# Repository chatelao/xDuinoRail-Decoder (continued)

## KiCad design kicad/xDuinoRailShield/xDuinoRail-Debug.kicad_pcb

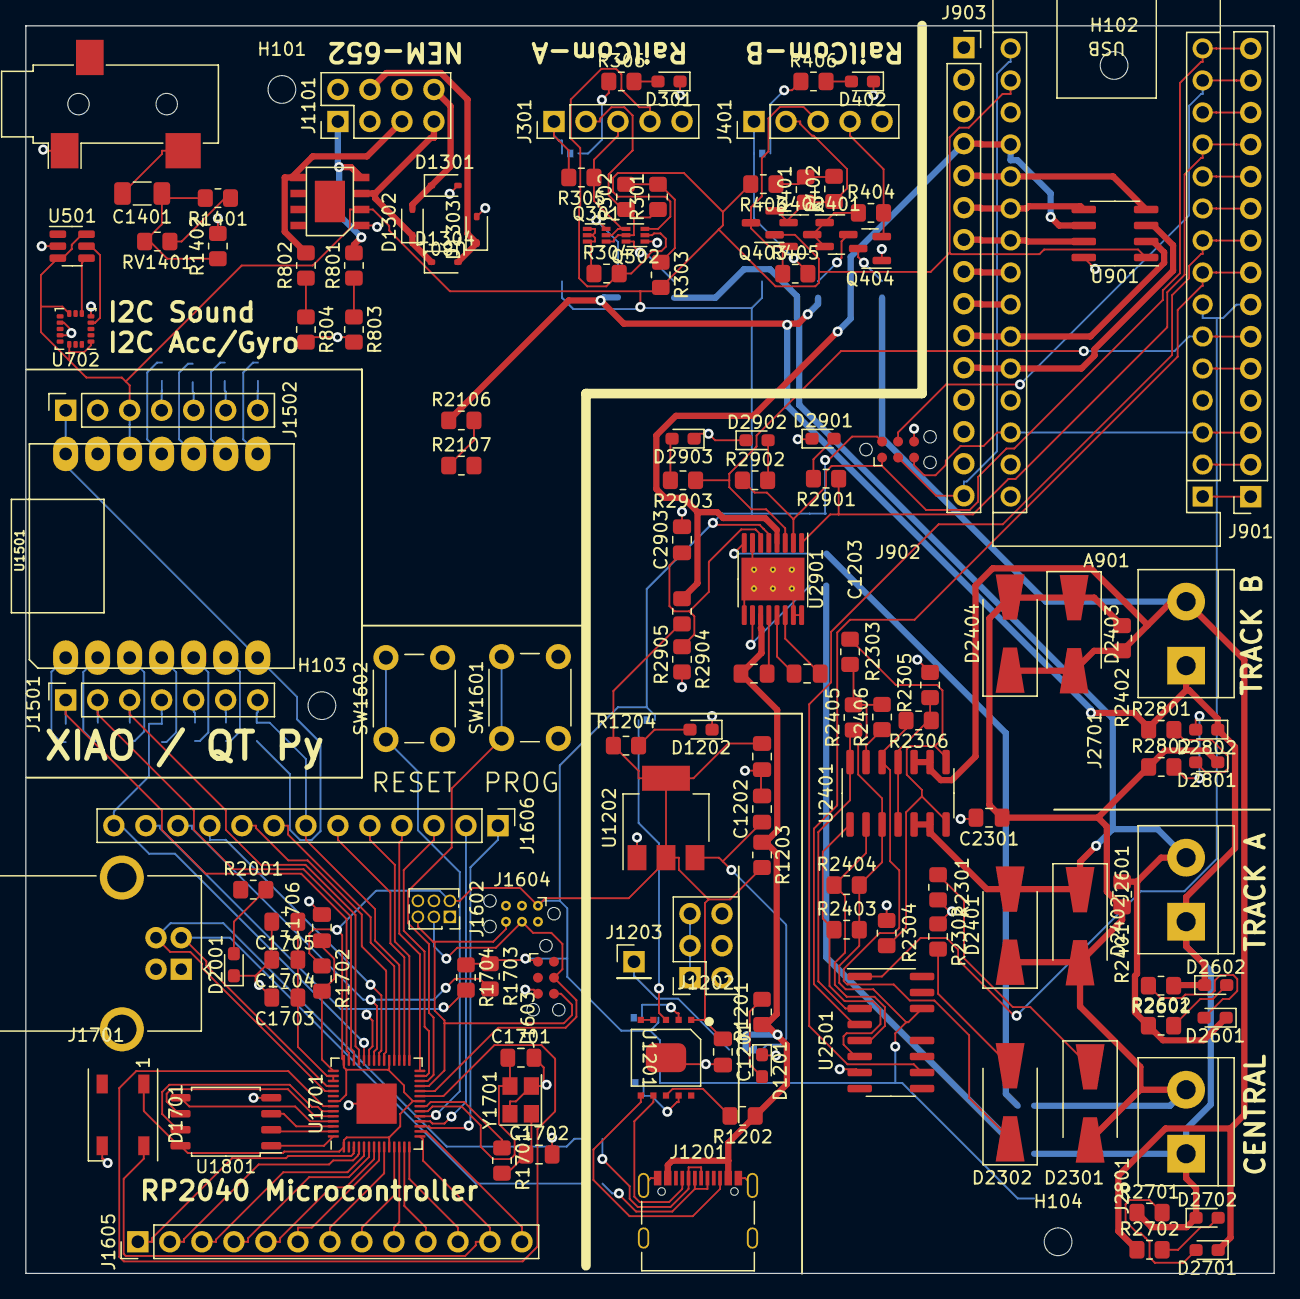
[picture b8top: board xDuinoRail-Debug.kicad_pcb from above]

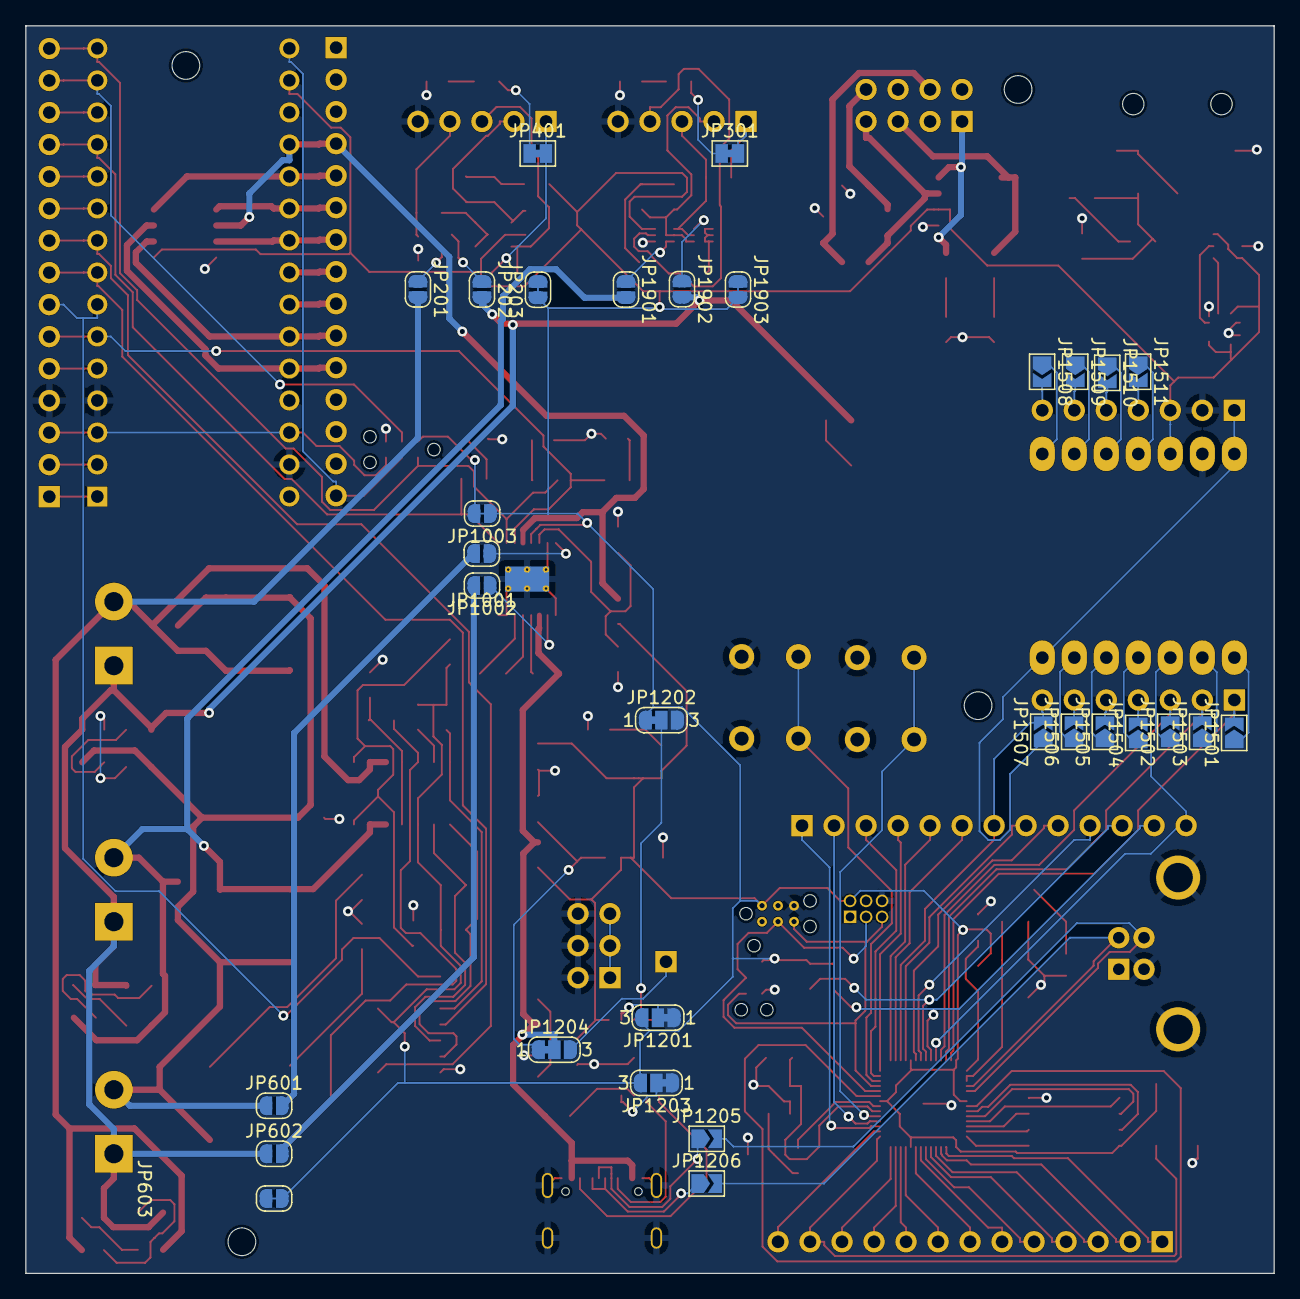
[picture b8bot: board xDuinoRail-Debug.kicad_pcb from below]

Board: 2 copper layers, 99.1 x 99.0 mm, 170 parts (31 on the bottom side), 168 nets.

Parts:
A901: Arduino_Nano_Every; Arduino_Nano
C1201, C1202: 1uF; C_0805_2012Metric_Pad1.18x1.45mm_HandSolder
C1203, C2301: 47uF; C_0805_2012Metric_Pad1.18x1.45mm_HandSolder
C1401: 100uF; C_1206_3216Metric_Pad1.33x1.80mm_HandSolder
C1701, C1702: 33p; C_0805_2012Metric_Pad1.18x1.45mm_HandSolder
C1703, C1704: 100n; C_0805_2012Metric_Pad1.18x1.45mm_HandSolder
C1705, C1706: 10u; C_0805_2012Metric_Pad1.18x1.45mm_HandSolder
C2901: 100nF; C_0805_2012Metric_Pad1.18x1.45mm_HandSolder
C2902, C2903: 22nF; C_0805_2012Metric_Pad1.18x1.45mm_HandSolder
D301, D402, D1201, D1202, D2001, D2601, D2602, D2701, D2702, D2801, D2802: LED; LED_0603_1608Metric_Pad1.05x0.95mm_HandSolder
D1301, D1302, D1303, D1304: 1N5819WS; D_SOD-323
D1701: WS2812B; LED_WS2812B_PLCC4_5.0x5.0mm_P3.2mm
D2301, D2302: SM4007; D_SMA-SMB_Universal_Handsoldering
D2401, D2402, D2403, D2404: SS54; D_SMA-SMB_Universal_Handsoldering
D2901: LED_RED; LED_0603_1608Metric_Pad1.05x0.95mm_HandSolder
D2902: LED_YELLOW; LED_0603_1608Metric_Pad1.05x0.95mm_HandSolder
D2903: LED_GREEN; LED_0603_1608Metric_Pad1.05x0.95mm_HandSolder
H101, H102, H103, H104: MountingHole; MountingHole_2.2mm_M2
J301, J401: Conn_01x05; PinHeader_1x05_P2.54mm_Vertical
J901, J903: Conn_01x15; PinSocket_1x15_P2.54mm_Vertical
J902, J1603: Conn_ARM_SWD_TagConnect_TC2030-NL; Tag-Connect_TC2030-IDC-NL_2x03_P1.27mm_Vertical
J1101: Conn_02x04_Counter_Clockwise; PinHeader_2x04_P2.54mm_Vertical
J1201: USB_C_Receptacle_USB2.0_14P; USB_C_Receptacle_Palconn_UTC16-G
J1202: Conn_02x03_Odd_Even; PinSocket_2x03_P2.54mm_Vertical
J1203: Conn_01x01; PinHeader_1x01_P2.54mm_Vertical
J1401: AudioJack2_Ground; Jack_3.5mm_CUI_SJ-3523-SMT_Horizontal
J1501, J1502: Conn_01x07; PinSocket_1x07_P2.54mm_Vertical
J1602: Conn_02x03_Odd_Even; PinSocket_2x03_P1.27mm_Vertical
J1604: Conn_ARM_SWD_TagConnect_TC2030-NL; Tag-Connect_TC2030-IDC-NL_2x03_P1.27mm_Vertical-WithHoles
J1605, J1606: Conn_01x13; PinHeader_1x13_P2.54mm_Vertical
J1701: USB_B; USB_B_OST_USB-B1HSxx_Horizontal
J2601, J2701, J2801: Screw_Terminal_01x02; TerminalBlock_bornier-2_P5.08mm
JP201, JP202, JP203, JP601, JP602, JP603, JP1001, JP1002, JP1003, JP1901, JP1902, JP1903: SolderJumper_2_Open; SolderJumper-2_P1.3mm_Open_RoundedPad1.0x1.5mm
JP301, JP401: SolderJumper_2_Bridged; SolderJumper-2_P1.3mm_Bridged_Pad1.0x1.5mm
JP1201: CFG2; SolderJumper-3_P1.3mm_Bridged12_RoundedPad1.0x1.5mm_NumberL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
JP1202: CFG3; SolderJumper-3_P1.3mm_Bridged12_RoundedPad1.0x1.5mm_NumberL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
JP1203, JP1204: CFG1; SolderJumper-3_P1.3mm_Bridged12_RoundedPad1.0x1.5mm_NumberL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
JP1205, JP1206, JP1501, JP1502, JP1503, JP1504, JP1505, JP1506, JP1507, JP1508, JP1509, JP1510, JP1511: SolderJumper_2_Open; SolderJumper-2_P1.3mm_Open_TrianglePad1.0x1.5mm
Q301, Q302: BC847BVN; SOT-563
Q401, Q404: S8050; SOT-23
Q402, Q403: S8550; SOT-23
R301, R302, R303, R401, R402, R403: 10R; R_0805_2012Metric_Pad1.20x1.40mm_HandSolder
R304, R305, R404, R405, R1202, R1401, R1402, R1703, R1704, R2106, R2107, R2403, R2404, R2405, R2406: 10k; R_0805_2012Metric_Pad1.20x1.40mm_HandSolder
R306, R406, R1204: 100R; R_0805_2012Metric_Pad1.20x1.40mm_HandSolder
R801, R802: 6k8; R_0805_2012Metric_Pad1.20x1.40mm_HandSolder
R803, R804, R1201, R1203, R1701, R2304: 1k; R_0805_2012Metric_Pad1.20x1.40mm_HandSolder
R1702, R2301, R2302: 220R; R_0805_2012Metric_Pad1.20x1.40mm_HandSolder
R2001, R2901, R2902, R2903: 470R; R_0805_2012Metric_Pad1.20x1.40mm_HandSolder
R2303: 180K; R_0805_2012Metric_Pad1.20x1.40mm_HandSolder
R2305: 820R; R_0805_2012Metric_Pad1.20x1.40mm_HandSolder
R2306: 33k; R_0805_2012Metric_Pad1.20x1.40mm_HandSolder
R2401, R2402: 1R8; R_0805_2012Metric_Pad1.20x1.40mm_HandSolder
R2601, R2602, R2701, R2702, R2801, R2802: 3k3; R_0805_2012Metric_Pad1.20x1.40mm_HandSolder
R2904: 1k5; R_0805_2012Metric_Pad1.20x1.40mm_HandSolder
R2905: 47k; R_0805_2012Metric_Pad1.20x1.40mm_HandSolder
RV1401: 10k; R_0805_2012Metric_Pad1.20x1.40mm_HandSolder
SW1601, SW1602: SW_Push; SW_PUSH_6mm
U501: MCP4725xxx-xCH; SOT-23-6
U702: LIS3DH; LGA-16_3x3mm_P0.5mm_LayoutBorder3x5y
U801: BDR6133
U901: ATtiny402-SS; SOIC-8_3.9x4.9mm_P1.27mm
U1201: CH224K
U1202: AMS1117-3.3; SOT-223-3_TabPin2
U1501: MOUDLE-SEEEDUINO-XIAO-ESP32C3; MOUDLE14P-SMD-2.54-21X17.8MM
U1701: RP2040; QFN-56-1EP_7x7mm_P0.4mm_EP3.2x3.2mm
U1801: W25Q128JVS; SOIC-8_5.23x5.23mm_P1.27mm
U2401: LM339; SOIC-14_3.9x8.7mm_P1.27mm
U2501: 74HC02; SOIC-14-16_3.9x9.9mm_P1.27mm
U2901: DRV8874PWPR; HTSSOP-16-1EP_4.4x5mm_P0.65mm_EP3.4x5mm_Mask2.46x2.31mm_The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
Y1701: X322512MSB4SI; Crystal_SMD_3225-4Pin_3.2x2.5mm

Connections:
18mV: R2303.1, R2304.2, U2401.7 (+), U2401.8 (-)
+1V1: C1703.1, C1704.1, C1705.1, U1701.44 (VREG_IN), U1701.45 (VREG_VOUT)
+3V3: A901.17 (3V3), C1201.1, C1203.1, D1701.1 (VDD), J902.2 (SWDIO), J1502.3, J1602.2, J1603.1 (VCC), J1604.1 (VCC), JP203.1 (A), JP203.2 (B), JP603.1 (A), JP603.2 (B), JP1003.1 (A), JP1003.2 (B), JP1201.3 (B), JP1202.1 (A), JP1203.3 (B), JP1903.1 (A), JP1903.2 (B), Q302.3 (C2), Q403.1 (E), R303.2, R403.2, R1203.2, R1204.1, R1702.1, R1703.1, R1704.1, R2303.2, R2403.2, R2404.2, R2405.2, R2406.2, R2905.1, U501.3 (VDD), U501.6 (A0), U702.1 (VDD_IO), U702.8 (CS), U702.14 (VDD), U801.2 (VCC), U901.1 (VCC), U1201.1 (VDD), U1202.2 (VO), U1501.12 (3V3), U1701.1 (IOVDD), U1701.10 (IOVDD), U1701.22 (IOVDD), U1701.33 (IOVDD), U1701.42 (IOVDD), U1701.49 (IOVDD), U1801.8 (VCC), U2401.3 (V+), U2501.14 (VCC), U2901.5 (VRef)
+5V: J1502.1, JP1507.1 (A), U1501.7 (A6_TX), U1501.14 (5V)
+U: D1302.1 (K), D1304.1 (K), J1101.7, U801.3 (VM)
+VBUS_H: C2901.2, J1201.A4 (VBUS), J1201.A9 (VBUS), J1201.B4 (VBUS), J1201.B9 (VBUS), JP1204.2 (C), R1201.1, R1202.1, R1203.1, U2901.11 (VM)
-18mV: R2305.1, R2306.1, U2401.4 (-), U2401.11 (+)
-750mV: D2302.1 (K), R2306.2, U2401.12 (V-)
/ADC0: R801.1, R803.1
/ADC1: R802.1, R804.1
/AMP_MOTOR0: J1101.1, R801.2, U801.4 (OUTA)
/AMP_MOTOR1: J1101.5, R802.2, U801.5 (OUTB)
/CENTRAL0: JP601.2 (B), JP1001.2 (B)
/CENTRAL1: JP602.2 (B), JP1002.2 (B)
/CENTRAL_MAIN0: C2301.1, D2301.2 (A), D2401.1 (K), D2402.2 (A), D2403.1 (K), D2404.2 (A), D2801.1 (K), J2801.2, JP601.1 (A), R2401.2, R2402.2, R2802.1
/CENTRAL_MAIN1: D2602.1 (K), D2702.1 (K), D2802.1 (K), J2601.1, J2701.1, J2801.1, JP202.2 (B), JP602.1 (A), JP1902.2 (B), R2106.1, R2601.1, R2701.1, R2801.1
/CN_A0: A901.19 (A0), J903.4, R2905.2, U901.6 (~RESET/PA0), U2901.4 (nFAULT)
/CN_A1: A901.20 (A1), J903.5, U901.4 (PA1)
/CN_A2: A901.21 (A2), J903.6, U901.5 (PA2)
/CN_A3: A901.22 (A3), J903.7, U901.7 (PA3)
/CN_A4: A901.23 (SDA/A4), J903.8
/CN_A5: A901.24 (SCL/A5), J903.9
/CN_A6: A901.25 (A6), J903.10, U901.2 (PA6)
/CN_A7: A901.26 (A7), J903.11, U901.3 (PA7)
/CN_D0: A901.1 (TX1), J901.1
/CN_D1: A901.2 (RX1), J901.2
/CN_D2: A901.5 (D2), J901.5
/CN_D3: A901.6 (D3), J901.6, R2903.1, U2901.3 (nSleep)
/CN_D4: A901.7 (D4), J901.7, U2501.1
/CN_D5: A901.8 (D5), J901.8, U2501.4
/CN_D6: A901.9 (D6), J901.9, U2501.10
/CN_D7: A901.10 (D7), J901.10
/CN_D8: A901.11 (D8), J901.11
/CN_D9: A901.12 (D9), J901.12, R2901.1, U2901.1 (EN/IN1)
/CN_D10: A901.13 (D10), J901.13
/CN_D11: A901.14 (MOSI), J901.14, J902.4 (SWCLK)
/CN_D12: A901.15 (MISO), J901.15, J902.1 (VCC), R2902.1, U2901.2 (PH/IN2)
/CN_D13: A901.16 (SCK), J902.3 (~RESET), J903.15
/CTRL_DRV0: JP1001.1 (A), U2901.8 (OUT1)
/CTRL_DRV1: JP1002.1 (A), U2901.10 (OUT2)
/DCC0: D1301.1 (K), D1302.2 (A), J1101.8
/DCC1: D1303.1 (K), D1304.2 (A), J1101.4
/GPIO24: U501.4 (SDA), U702.6 (SDA/SDI/SDO)
/GPIO25: U501.5 (SCL), U702.4 (SCL/SPC)
/I2C0: J1501.6, JP1506.2 (B)
/I2C1: J1501.5, JP1505.2 (B)
/M_GPIO1: J1605.1, U1701.3 (GPIO1)
/M_GPIO2: J1605.2, U1701.4 (GPIO2)
/M_GPIO3: J1605.3, U1701.5 (GPIO3)
/M_GPIO4: J1605.4, U1701.6 (GPIO4)
/M_GPIO5: J1605.5, U1701.7 (GPIO5)
/M_GPIO6: J1605.6, U1701.8 (GPIO6)
/M_GPIO7: J1605.7, U1701.9 (GPIO7)
/M_GPIO8: J1605.8, U1701.11 (GPIO8)
/M_GPIO9: J1605.9, U1701.12 (GPIO9)
/M_GPIO10: J1605.10, U1701.13 (GPIO10)
/M_GPIO11: J1605.11, U1701.14 (GPIO11)
/M_GPIO12: D1701.4 (DIN), J1605.12, U1701.15 (GPIO12)
/M_GPIO13: J1605.13, U1701.16 (GPIO13)
/M_GPIO14: J1606.1, U1701.17 (GPIO14)
/M_GPIO15: J1606.2, U1701.18 (GPIO15)
/M_GPIO16: J1606.3, U1701.27 (GPIO16)
/M_GPIO17: J1606.4, U1701.28 (GPIO17)
/M_GPIO18: J1606.5, U1701.29 (GPIO18)
/M_GPIO19: J1606.6, U1701.30 (GPIO19)
/M_GPIO20: J1501.7, J1606.7, JP1507.2 (B), U1701.31 (GPIO20)
/M_GPIO21: J1606.8, U1701.32 (GPIO21)
/M_GPIO22: J1606.9, U1701.34 (GPIO22)
/M_GPIO23: J1606.10, U1701.35 (GPIO23)
/M_GPIO24: J1606.11, R1703.2, U1701.36 (GPIO24)
/M_GPIO25: J1606.12, R1704.2, U1701.37 (GPIO25)
/M_GPIO26: J1501.4, J1606.13, JP1504.2 (B), U1701.38 (GPIO26_ADC0)
/M_GPIO27: J1501.3, JP1502.2 (B), U1701.39 (GPIO27_ADC1)
/M_GPIO28: J1501.2, JP1503.2 (B), U1701.40 (GPIO28_ADC2)
/M_GPIO29: J1501.1, JP1501.2 (B), U1701.41 (GPIO29_ADC3)
/TRACK_A0: D2401.2 (A), D2402.1 (K), D2601.1 (K), J2601.2, JP1901.2 (B), R2401.1, R2602.1, U2401.5 (+), U2401.6 (-)
/TRACK_B0: D2403.2 (A), D2404.1 (K), D2701.1 (K), J2701.2, JP201.2 (B), R2402.1, R2702.1, U2401.9 (+), U2401.10 (-)
/USB_DM: J1701.2 (D-), JP1206.2 (B), U1701.46 (USB_DM)
/USB_DP: J1701.3 (D+), JP1205.2 (B), U1701.47 (USB_DP)
/X_A7: J1502.7, JP1508.2 (B)
/X_A8: J1502.6, JP1509.2 (B)
/X_A9: J1502.5, JP1510.2 (B)
/X_A10: J1502.4, JP1511.2 (B)
/audio-35jack/DAC_IN: R1401.1, RV1401.1
/centrale-railcom-feedback/central_railcom-detector/RAILCOM_A0: R2404.1, U2401.2, U2501.5
/centrale-railcom-feedback/central_railcom-detector/RAILCOM_A1: R2403.1, U2401.1, U2501.6
/centrale-railcom-feedback/central_railcom-detector/RAILCOM_B0: R2406.1, U2401.13
/centrale-railcom-feedback/central_railcom-detector/RAILCOM_B1: R2405.1, U2401.14, U2501.3
/centrale_nano/RESET: A901.3 (~RESET), A901.28 (~RESET), J901.3, J902.5 (GND)
/mcu/BOOTSEL: SW1602.1, U1701.19 (TESTEN)
/mcu/RESET: SW1601.1, U1701.26 (RUN)
/mcu/SCK: U1701.52 (QSPI_SCLK), U1801.6 (CLK)
/mcu/SD0: U1701.53 (QSPI_SD0), U1801.5 (DI(IO0))
/mcu/SD1: U1701.55 (QSPI_SD1), U1801.2 (DO(IO1))
/mcu/SD2: U1701.54 (QSPI_SD2), U1801.3 (IO2)
/mcu/SD3: U1701.51 (QSPI_SD3), U1801.7 (IO3)
/mcu/SS: U1701.56 (QSPI_SS), U1801.1 (~CS)
/mcu/SWCLK: J1602.3, J1603.4 (SWCLK), J1604.4 (SWCLK), U1701.24 (SWCLK)
/mcu/SWD: J1602.5, J1603.6 (SWO), J1604.6 (SWO), U1701.25 (SWD)
/rails_signal_feedback_dcc-railcom-8x50/DCC0: JP201.1 (A), Q404.3 (C)
/rails_signal_feedback_dcc-railcom-8x50/DCC1: JP202.1 (A), Q401.3 (C)
/rails_signal_feedback_dcc-railcom-8x50/RAILCOM_DATA: J401.1, JP401.2 (B), R405.2
/rails_signal_feedback_dcc-railcom-8x50/RC_CURR: J401.2, Q402.1 (E), Q403.2 (B), R401.1, R402.1
/rails_signal_feedback_dcc-railcom-8x50/RC_FB_IN: J401.3, Q402.2 (B), Q403.3 (C), R405.1
/rails_signal_feedback_dcc-railcom-8x50/RC_ON_OFF: J401.4, Q404.2 (B), R404.2
/rails_signal_feedback_dcc-railcom-8x50/RC_SIGNAL: Q401.1 (E), Q401.2 (B), Q402.3 (C), R404.1
/rails_signal_feedback_dcc-railcom_BC8x7/DCC0: JP1901.1 (A), Q302.6 (C1)
/rails_signal_feedback_dcc-railcom_BC8x7/DCC1: JP1902.1 (A), Q301.6 (C1)
/rails_signal_feedback_dcc-railcom_BC8x7/RAILCOM_DATA: J301.1, JP301.2 (B), R305.2
/rails_signal_feedback_dcc-railcom_BC8x7/RC_CURR: J301.2, Q301.4 (E2), Q302.5 (B2), R301.1, R302.1
/rails_signal_feedback_dcc-railcom_BC8x7/RC_FB_IN: J301.3, Q301.5 (B2), Q302.4 (E2), R305.1
/rails_signal_feedback_dcc-railcom_BC8x7/RC_ON_OFF: J301.4, Q302.2 (B1), R304.2
/rails_signal_feedback_dcc-railcom_BC8x7/RC_SIGNAL: Q301.1 (E1), Q301.2 (B1), Q301.3 (C2), R304.1
/usb-c_power_dc-dc-15V_3v3-1A/+VBUS_H_LDO: C1202.1, JP1204.1 (A), U1202.3 (VI)
/usb-c_power_dc-dc-15V_3v3-1A/CC1: J1201.A5 (CC1), U1201.7 (CC1)
/usb-c_power_dc-dc-15V_3v3-1A/CC2: J1201.B5 (CC2), U1201.6 (CC2)
/usb-c_power_dc-dc-15V_3v3-1A/CFG1: JP1203.2 (C), U1201.9 (CFG1)
/usb-c_power_dc-dc-15V_3v3-1A/CFG2: JP1201.2 (C), U1201.2 (CFG2)
/usb-c_power_dc-dc-15V_3v3-1A/CFG3: JP1202.2 (C), U1201.3 (CFG3)
/usb-c_power_dc-dc-15V_3v3-1A/VBUS: J1202.1, J1202.3, J1202.5
/usb-c_power_dc-dc-15V_3v3-1A/VEXT: J1203.1, JP1204.3 (B)
/xiao_decoder/X_A0: JP1501.1 (A), U1501.1 (A0)
/xiao_decoder/X_A1: JP1503.1 (A), U1501.2 (A1)
/xiao_decoder/X_A2: JP1502.1 (A), U1501.3 (A2)
/xiao_decoder/X_A3: JP1504.1 (A), U1501.4 (A3)
/xiao_decoder/X_A4: JP1505.1 (A), U1501.5 (A4_SDA)
/xiao_decoder/X_A5: JP1506.1 (A), U1501.6 (A5_SCL)
/xiao_decoder/X_A7: JP1508.1 (A), U1501.8 (A7_RX)
/xiao_decoder/X_A8: JP1509.1 (A), U1501.9 (A8_SCK)
/xiao_decoder/X_A9: JP1510.1 (A), U1501.10 (A9_MISO)
/xiao_decoder/X_A10: JP1511.1 (A), U1501.11 (A10_MOSI)
GND: A901.4 (GND), A901.29 (GND), C1201.2, C1202.2, C1203.2, C1701.2, C1702.2, C1703.2, C1704.2, C1705.2, C1706.2, C2301.2, C2903.2, D301.1 (K), D402.1 (K), D1201.1 (K), D1202.1 (K), D1301.2 (A), D1303.2 (A), D1701.3 (VSS), D2001.1 (K), D2901.1 (K), D2902.1 (K), D2903.1 (K), J301.5, J401.5, J901.4, J902.6 (SWO), J1201.A1 (GND), J1201.A12 (GND), J1201.B1 (GND), J1201.B12 (GND), J1201.S1 (SHIELD), J1202.2, J1202.4, J1202.6, J1401.S, J1502.2, J1602.6, J1603.5 (GND), J1604.5 (GND), J1701.4 (GND), J1701.5 (Shield), JP1201.1 (A), JP1202.3 (B), JP1203.1 (A), Q302.1 (E1), Q404.1 (E), R803.2, R804.2, R1402.2, R2301.2, R2302.1, R2304.1, R2305.2, R2904.2, SW1601.2, SW1602.2, U501.2 (VSS), U702.5 (GND), U702.10 (GND), U702.12 (GND), U801.1 (GND), U901.8 (GND), U1201.0 (GND), U1202.1 (GND), U1501.13 (GND), U1701.57 (GND), U1801.4 (GND), U2501.7 (GND), U2901.7 (IMODE), U2901.9 (GND), U2901.15 (GND), U2901.16 (PMODE), U2901.17 (GND), Y1701.2, Y1701.4
unnamed: C1401.1, R1401.2, R1402.1, RV1401.2
unnamed: C1401.2, J1401.T
unnamed: C1702.1, R1701.2, Y1701.1
unnamed: D301.2 (A), R306.2
unnamed: D402.2 (A), R406.2
unnamed: D1201.2 (A), R1201.2
unnamed: D1202.2 (A), R1204.2
unnamed: D2001.2 (A), R2001.2
unnamed: D2301.1 (K), R2301.1
unnamed: D2302.2 (A), R2302.2
unnamed: D2601.2 (A), R2601.2
unnamed: D2602.2 (A), R2602.2
unnamed: D2701.2 (A), R2701.2
unnamed: D2702.2 (A), R2702.2
unnamed: D2801.2 (A), R2801.2
unnamed: D2802.2 (A), R2802.2
unnamed: D2901.2 (A), R2901.2
unnamed: D2902.2 (A), R2902.2
unnamed: D2903.2 (A), R2903.2
unnamed: JP301.1 (A), R306.1
unnamed: JP401.1 (A), R406.1
unnamed: J1201.A7 (D-), J1201.B7 (D-), JP1205.1 (A)
unnamed: J1201.A6 (D+), J1201.B6 (D+), JP1206.1 (A)
unnamed: R301.2, R302.2, R303.1
unnamed: R401.2, R402.2, R403.1
unnamed: R2106.2, R2107.1
unnamed: U1201.4 (DP), U1201.5 (DM)
unnamed: R1202.2, U1201.8 (VBUS)
unnamed: C1706.1, R1702.2, U1701.43 (ADC_AVDD)
unnamed: U1701.23 (DVDD), U1701.50 (DVDD)
unnamed: C1701.1, U1701.20 (XIN), Y1701.3
unnamed: R1701.1, U1701.21 (XOUT)
unnamed: C2902.1, U2901.13 (CPH)
unnamed: C2902.2, U2901.14 (CPL)
unnamed: C2903.1, R2904.1, U2901.6 (IPROPI)
unnamed: C2901.1, U2901.12 (VCP)

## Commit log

2023-11-27 Backlink to CADLAB.io has been added.
2023-11-27 Add - Board to the repository
    The beginning
2023-12-04 Heavy refactoring
2023-12-05 Shield extracted
2023-12-05 Add more extractor
2023-12-11 More options, more Partnumbers
2023-12-12 Leiterbahnbreiten anpassen
2023-12-12 Edge cuts
2023-12-12 Another iteration on the layout
2023-12-12 Power Rails added to Arduino IO board
2023-12-12 Add Analog signal extraction draft
2023-12-18 xXiaoCentralMini
2023-12-21 xDuinoRailControl
2023-12-21 Add encoder
2023-12-30 More improvements
2023-12-31 More nice changes
2024-01-01 More busses added
2024-01-01 Draft of loco decoder
2024-01-03 A lot of fixes
2024-01-04 Final version
2024-01-06 Refactoring & Sound
2024-01-14 More refactoring
2024-01-23 More stuff
2024-01-23 Neue Breakouts
2024-02-09 Many exiting news
